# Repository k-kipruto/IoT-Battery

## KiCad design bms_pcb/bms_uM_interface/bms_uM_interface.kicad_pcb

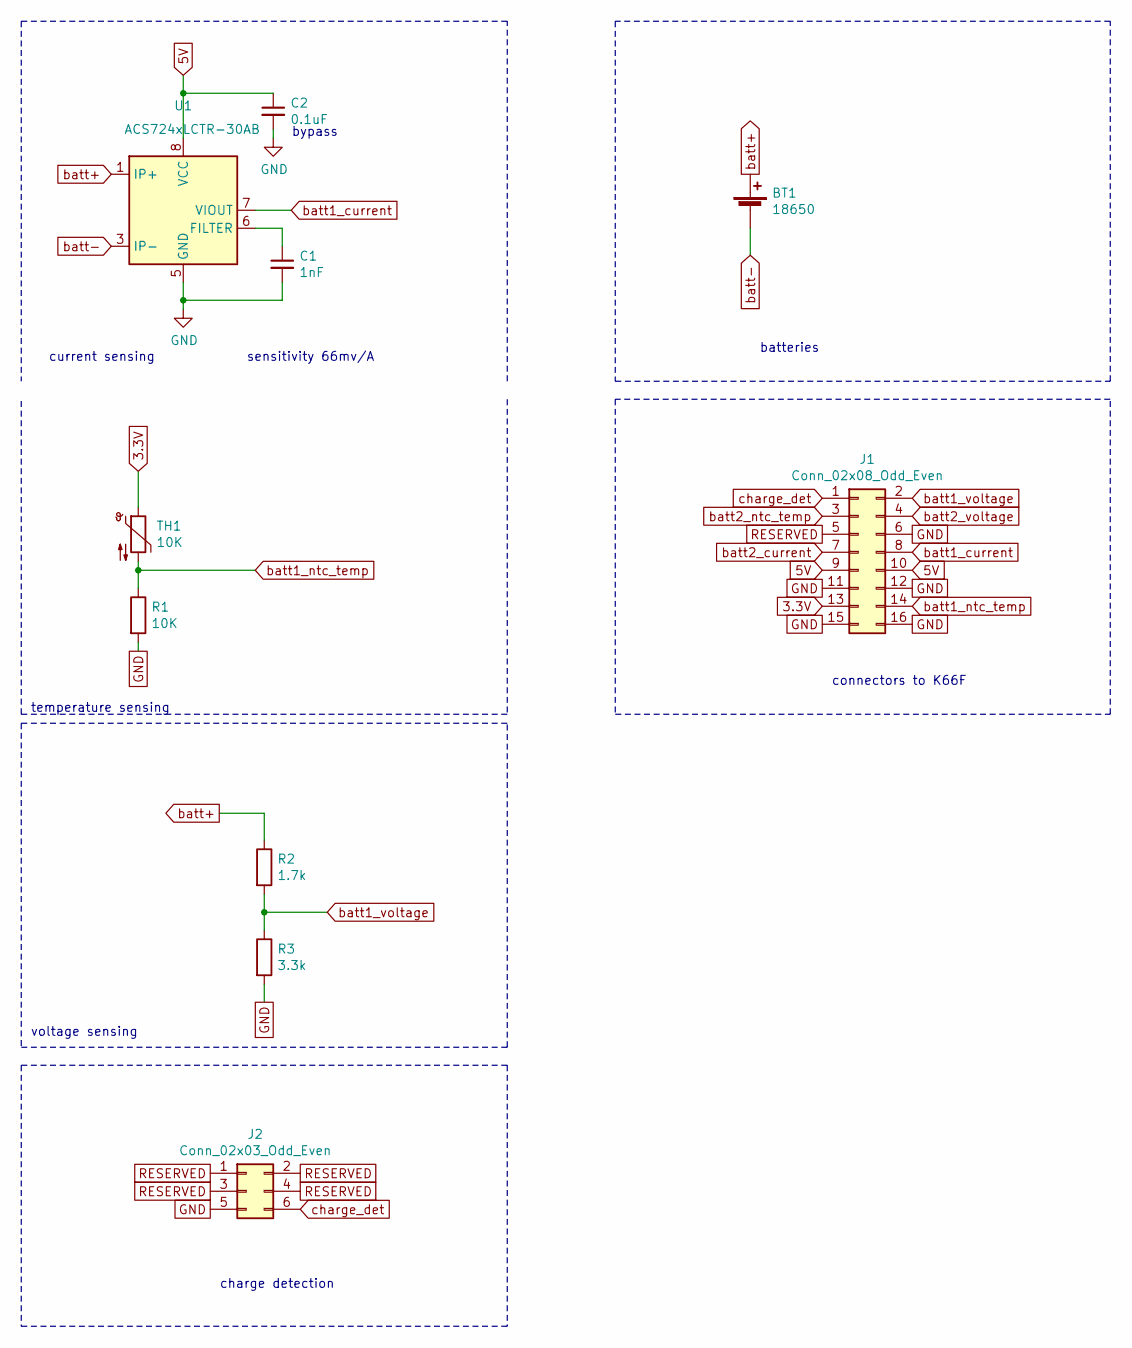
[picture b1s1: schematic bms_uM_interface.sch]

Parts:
BT1: 18650; BatteryHolder_MPD_BH-18650-PC2
C1: 1nF; C_0603_1608Metric_Pad1.05x0.95mm_HandSolder
C2: 0.1uF; C_0603_1608Metric_Pad1.05x0.95mm_HandSolder
J1: Conn_02x08_Odd_Even; PinSocket_2x08_P2.54mm_Vertical
J2: Conn_02x03_Odd_Even; PinSocket_2x03_P2.54mm_Vertical
R1: 10K; R_0603_1608Metric
R2: 1.7k; R_0603_1608Metric
R3: 3.3k; R_0603_1608Metric
TH1: 10K; C_Disc_D8.0mm_W5.0mm_P5.00mm
U1: ACS724xLCTR-30AB; SOIC-8_3.9x4.9mm_P1.27mm

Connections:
3.3V: J1.13, TH1.1
5V: C2.1, J1.9, J1.10, U1.8 (VCC)
GND: C1.2, C2.2, J1.6, J1.11, J1.12, J1.15, J1.16, J2.5, R1.2, R3.2, U1.5 (GND)
unnamed: C1.1, U1.6 (FILTER)
RESERVED: J1.5, J2.1, J2.2, J2.3, J2.4
batt1_current: J1.8, U1.7 (VIOUT)
batt1_ntc_temp: J1.14, R1.1, TH1.2
batt1_voltage: J1.2, R2.2, R3.1
batt2_current: J1.7
batt2_ntc_temp: J1.3
batt2_voltage: J1.4
batt+: BT1.1 (+), R2.1, U1.1 (IP+), U1.2 (IP+)
batt-: BT1.2 (-), U1.3 (IP-), U1.4 (IP-)
charge_det: J1.1, J2.6

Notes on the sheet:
current sensing
bypass
batteries
temperature sensing
voltage sensing
charge detection
connectors to K66F
sensitivity 66mv/A

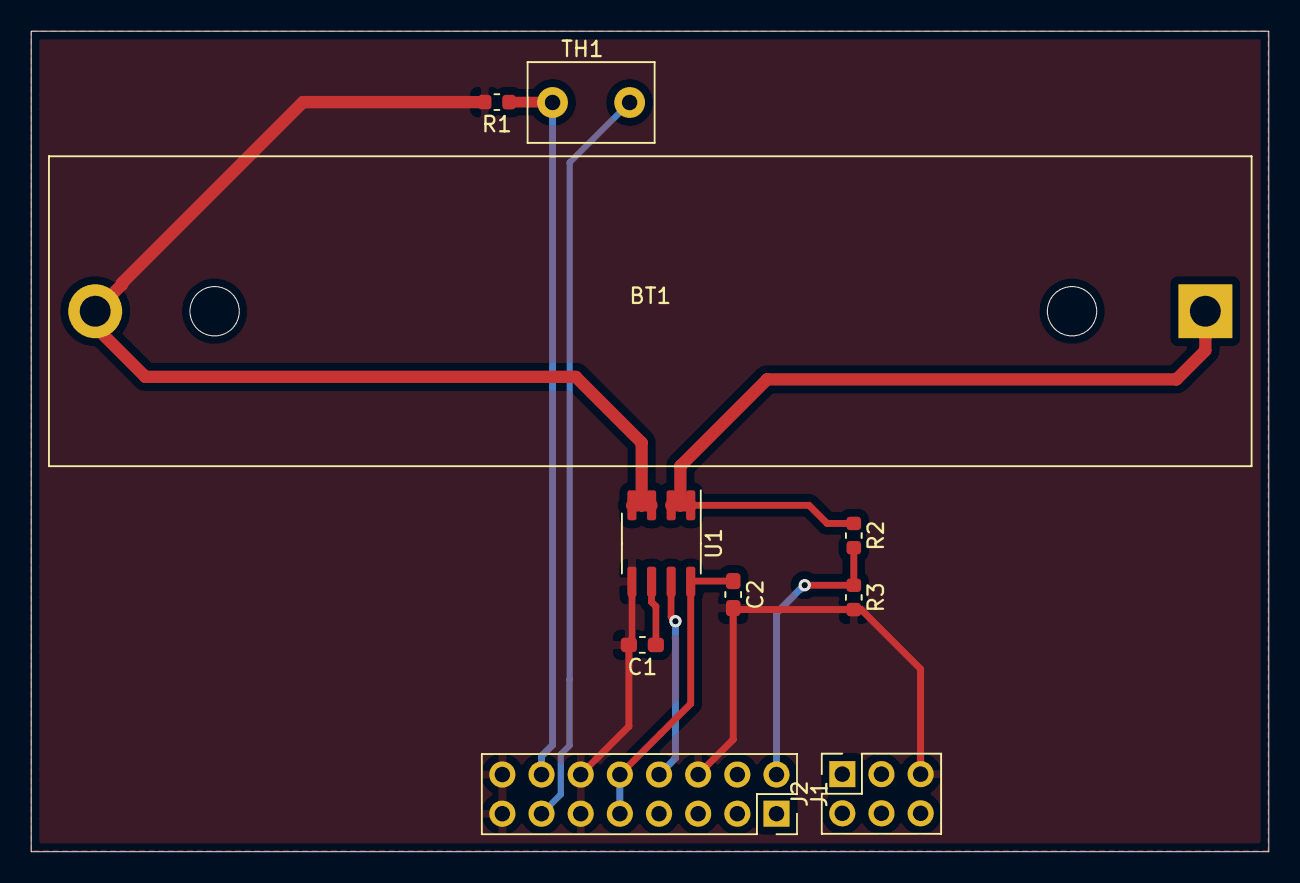
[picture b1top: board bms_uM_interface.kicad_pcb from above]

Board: 2 copper layers, 80.3 x 53.2 mm, 10 parts (0 on the bottom side), 11 nets.

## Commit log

2020-05-05 added mysql database for BMS
    added two tables to database one for battery information and the other for battery data
2020-05-05 addedt file for mbed
    will contain code necessary for collecting data from battery and uploading it to database
2020-05-05 made some few descriptions of php code
2020-05-05 fixed some errors on markdown format
2020-05-05 initial commit of bms_pcb
2020-05-08 remove redundacy
2020-05-08 remove redundancy
2021-01-21 test
